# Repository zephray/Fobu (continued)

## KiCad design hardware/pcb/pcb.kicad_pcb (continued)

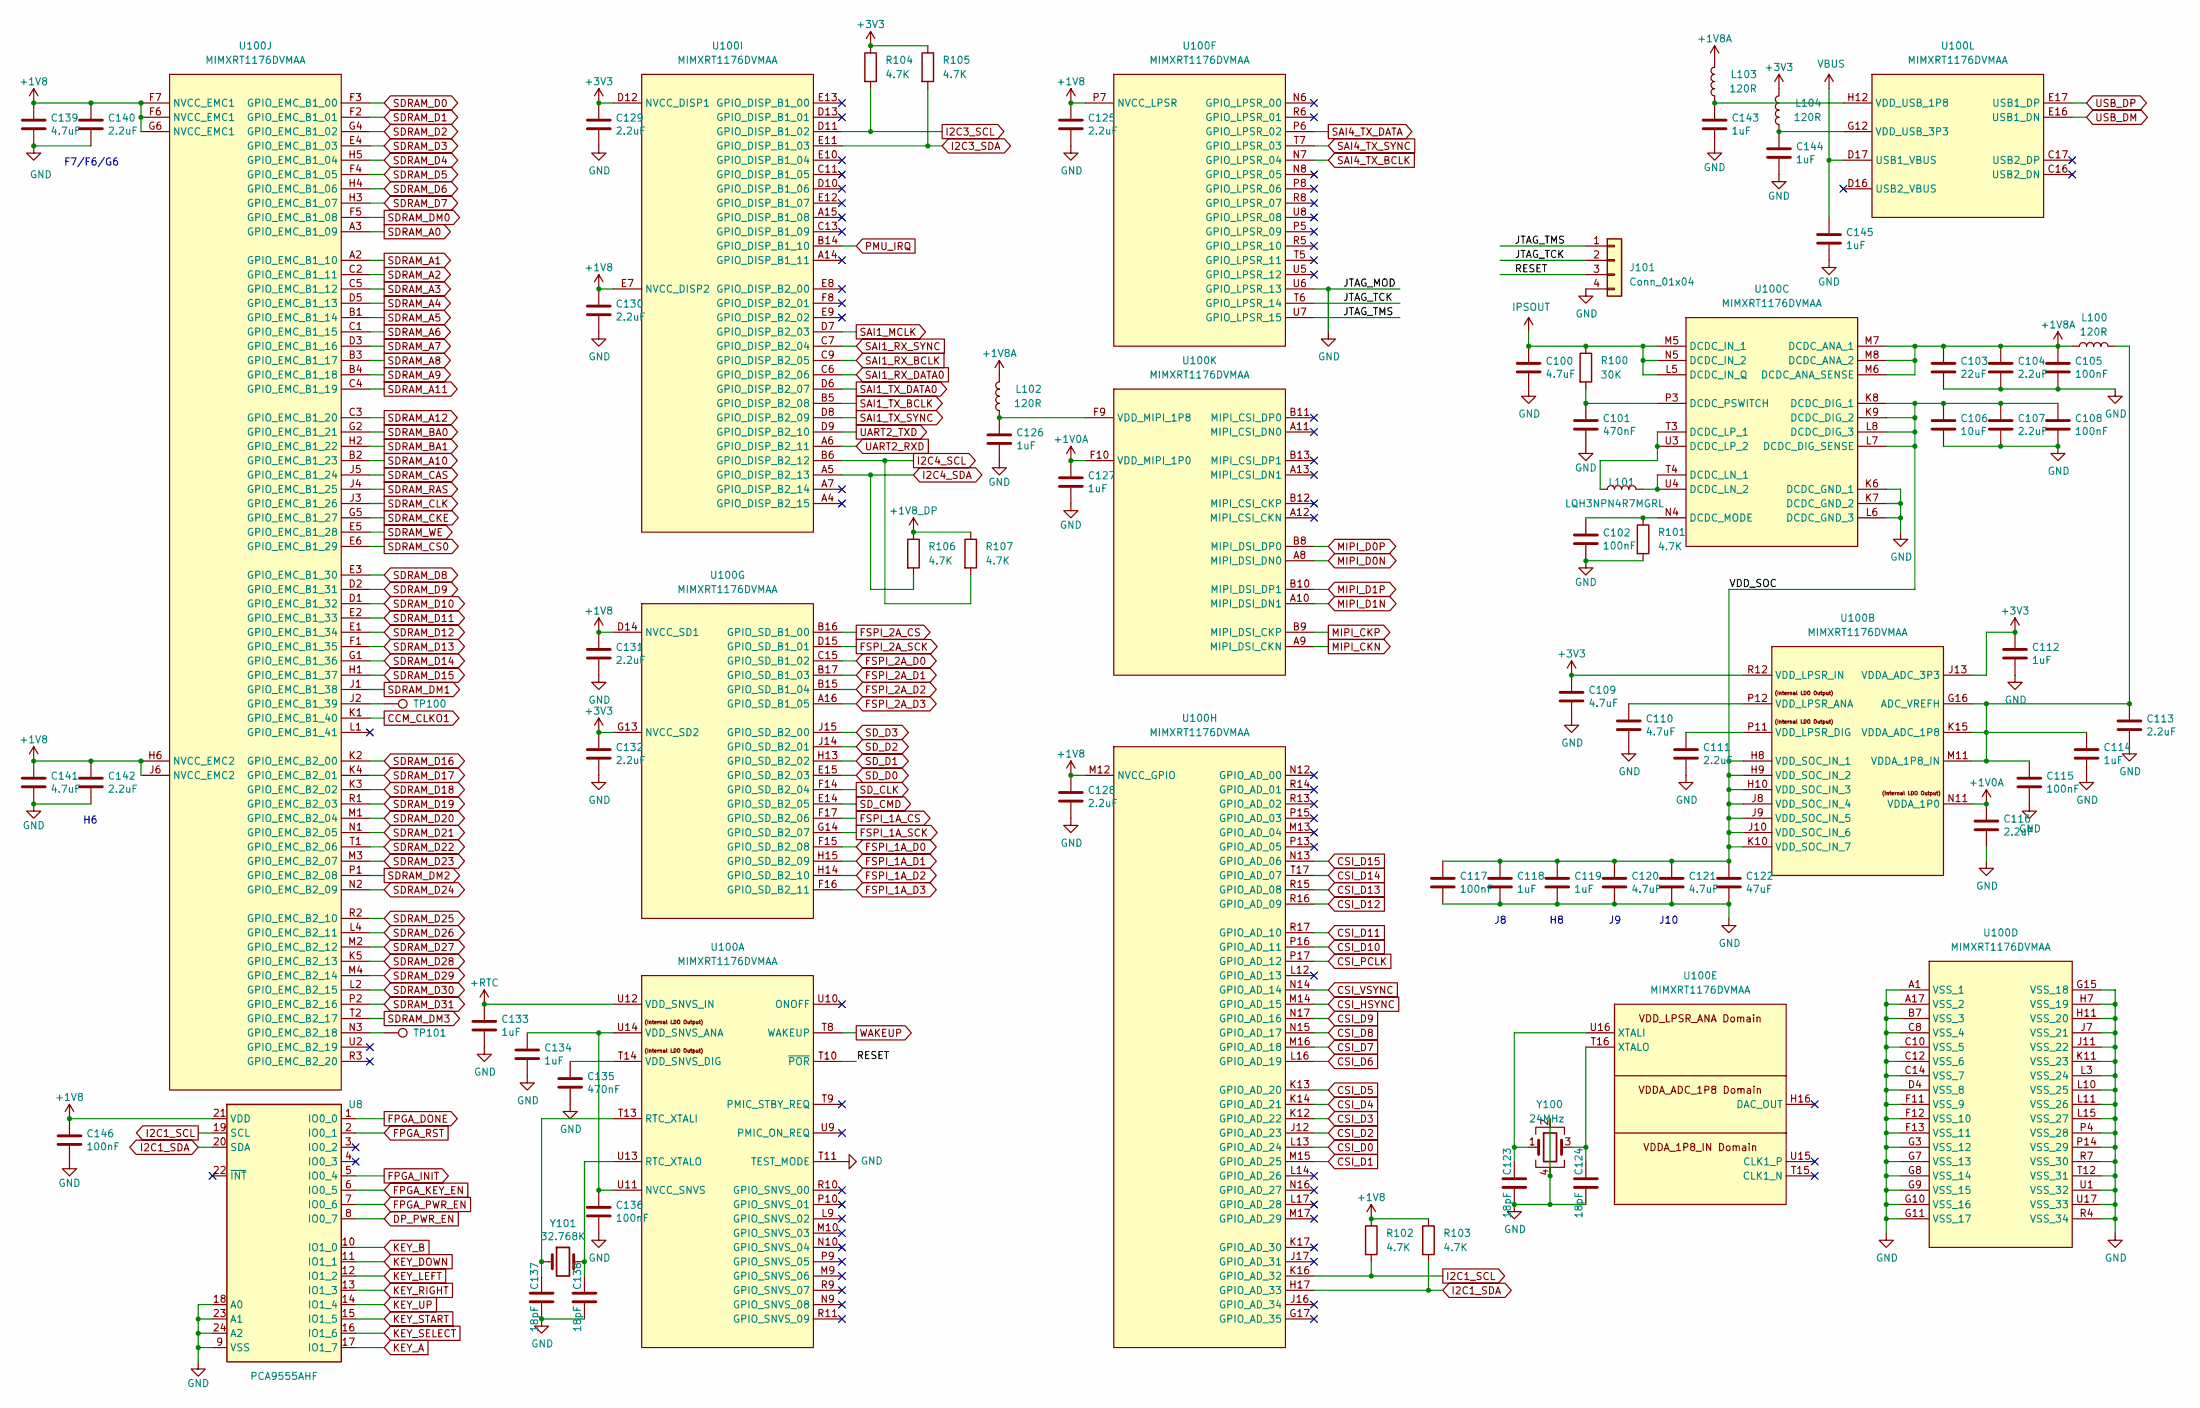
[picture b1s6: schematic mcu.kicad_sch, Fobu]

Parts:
C100, C109, C110, C120, C121, C139, C141: 4.7uF; C_0402_1005Metric
C101, C135: 470nF; C_0201_0603Metric
C102, C105, C108, C115, C117, C136, C146: 100nF; C_0201_0603Metric
C103: 22uF; C_0603_1608Metric
C104, C107, C111, C113, C116, C125, C128, C129, C130, C131, C132, C140, C142: 2.2uF; C_0402_1005Metric
C106: 10uF; C_0402_1005Metric
C112, C114, C118, C119, C126, C127, C133, C134, C143, C144, C145: 1uF; C_0402_1005Metric
C122: 47uF; C_0603_1608Metric
C123, C124, C137, C138: 18pF; C_0201_0603Metric
J101: Conn_01x04; PinHeader_1x04_P1.27mm_Vertical_SMD_Pin1Left
L100, L102, L103, L104: 120R; L_0402_1005Metric
L101: LQH3NPN4R7MGRL; L_Vishay_IHLP-1212
R100: 30K; R_0402_1005Metric
R101, R102, R103, R104, R105, R106, R107: 4.7K; R_0402_1005Metric
TP100, TP101: TestPoint; TestPoint_Pad_D0.5mm
U8: PCA9555AHF; HVQFN-24-1EP_4x4mm_P0.5mm_EP2.5x2.5mm
U100: MIMXRT1176DVMAA; BGA-289_17x17_14.0x14.0mm
Y100: 24MHz; Oscillator_SMD_Abracon_ASE-4Pin_3.2x2.5mm
Y101: 32.768K; Crystal_SMD_TXC_9HT11-2Pin_2.0x1.2mm_HandSoldering

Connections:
+1V0A: C116.1, C127.1, U100.F10 (VDD_MIPI_1P0), U100.N11 (VDDA_1P0)
+1V8: C125.1, C128.1, C130.1, C131.1, C139.1, C140.1, C141.1, C142.1, C146.1, R102.1, R103.1, U8.21 (VDD), U100.D14 (NVCC_SD1), U100.E7 (NVCC_DISP2), U100.F6 (NVCC_EMC1), U100.F7 (NVCC_EMC1), U100.G6 (NVCC_EMC1), U100.H6 (NVCC_EMC2), U100.J6 (NVCC_EMC2), U100.M12 (NVCC_GPIO), U100.P7 (NVCC_LPSR); also elsewhere on the board
+1V8A: C103.1, C104.1, C105.1, L100.1, L102.2, L103.2, U100.M6 (DCDC_ANA_SENSE), U100.M7 (DCDC_ANA_1), U100.M8 (DCDC_ANA_2); also elsewhere on the board
+1V8_DP: R106.1, R107.1; also elsewhere on the board
+3V3: C109.1, C112.1, C129.1, C132.1, L104.2, R104.1, R105.1, U100.D12 (NVCC_DISP1), U100.G13 (NVCC_SD2), U100.J13 (VDDA_ADC_3P3), U100.R12 (VDD_LPSR_IN); also elsewhere on the board
+RTC: C133.1, U100.U12 (VDD_SNVS_IN); also elsewhere on the board
/mcu/JTAG_TCK: J101.2, U100.T6 (GPIO_LPSR_14)
/mcu/JTAG_TMS: J101.1, U100.U7 (GPIO_LPSR_15)
/mcu/RESET: J101.3, U100.T10 (~POR)
/mcu/VDD_SOC: C106.1, C107.1, C108.1, C117.1, C118.1, C119.1, C120.1, C121.1, C122.1, U100.H8 (VDD_SOC_IN_1), U100.H9 (VDD_SOC_IN_2), U100.H10 (VDD_SOC_IN_3), U100.J8 (VDD_SOC_IN_4), U100.J9 (VDD_SOC_IN_5), U100.J10 (VDD_SOC_IN_6), U100.K8 (DCDC_DIG_1), U100.K9 (DCDC_DIG_2), U100.K10 (VDD_SOC_IN_7), U100.L7 (DCDC_DIG_SENSE), U100.L8 (DCDC_DIG_3)
CCM_CLKO1: U100.K1 (GPIO_EMC_B1_40)
CSI_D0: U100.L13 (GPIO_AD_24); also elsewhere on the board
CSI_D1: U100.M15 (GPIO_AD_25); also elsewhere on the board
CSI_D2: U100.J12 (GPIO_AD_23); also elsewhere on the board
CSI_D3: U100.K12 (GPIO_AD_22); also elsewhere on the board
CSI_D4: U100.K14 (GPIO_AD_21); also elsewhere on the board
CSI_D5: U100.K13 (GPIO_AD_20); also elsewhere on the board
CSI_D6: U100.L16 (GPIO_AD_19); also elsewhere on the board
CSI_D7: U100.M16 (GPIO_AD_18); also elsewhere on the board
CSI_D8: U100.N15 (GPIO_AD_17); also elsewhere on the board
CSI_D9: U100.N17 (GPIO_AD_16); also elsewhere on the board
CSI_D10: U100.P16 (GPIO_AD_11); also elsewhere on the board
CSI_D11: U100.R17 (GPIO_AD_10); also elsewhere on the board
CSI_D12: U100.R16 (GPIO_AD_09); also elsewhere on the board
CSI_D13: U100.R15 (GPIO_AD_08); also elsewhere on the board
CSI_D14: U100.T17 (GPIO_AD_07); also elsewhere on the board
CSI_D15: U100.N13 (GPIO_AD_06); also elsewhere on the board
CSI_HSYNC: U100.M14 (GPIO_AD_15); also elsewhere on the board
CSI_PCLK: U100.P17 (GPIO_AD_12); also elsewhere on the board
CSI_VSYNC: U100.N14 (GPIO_AD_14); also elsewhere on the board
DP_PWR_EN: U8.8 (IO0_7); also elsewhere on the board
FPGA_DONE: U8.1 (IO0_0); also elsewhere on the board
FPGA_INIT: U8.5 (IO0_4); also elsewhere on the board
FPGA_KEY_EN: U8.6 (IO0_5); also elsewhere on the board
FPGA_PWR_EN: U8.7 (IO0_6); also elsewhere on the board
FPGA_RST: U8.2 (IO0_1); also elsewhere on the board
FSPI_1A_CS: U100.F17 (GPIO_SD_B2_06); also elsewhere on the board
FSPI_1A_D0: U100.F15 (GPIO_SD_B2_08); also elsewhere on the board
FSPI_1A_D1: U100.H15 (GPIO_SD_B2_09); also elsewhere on the board
FSPI_1A_D2: U100.H14 (GPIO_SD_B2_10); also elsewhere on the board
FSPI_1A_D3: U100.F16 (GPIO_SD_B2_11); also elsewhere on the board
FSPI_1A_SCK: U100.G14 (GPIO_SD_B2_07); also elsewhere on the board
FSPI_2A_CS: U100.B16 (GPIO_SD_B1_00); also elsewhere on the board
FSPI_2A_D0: U100.C15 (GPIO_SD_B1_02); also elsewhere on the board
FSPI_2A_D1: U100.B17 (GPIO_SD_B1_03); also elsewhere on the board
FSPI_2A_D2: U100.B15 (GPIO_SD_B1_04); also elsewhere on the board
FSPI_2A_D3: U100.A16 (GPIO_SD_B1_05); also elsewhere on the board
FSPI_2A_SCK: U100.D15 (GPIO_SD_B1_01); also elsewhere on the board
GND: C100.2, C101.2, C102.2, C103.2, C104.2, C105.2, C106.2, C107.2, C108.2, C109.2, C110.2, C111.2, C112.2, C113.2, C114.2, C115.2, C116.2, C117.2, C118.2, C119.2, C120.2, C121.2, C122.2, C123.2, C124.2, C125.2, C126.2, C127.2, C128.2, C129.2, C130.2, C131.2, C132.2, C133.2, C134.2, C135.2, C136.2, C137.1, C138.1, C139.2, C140.2, C141.2, C142.2, C143.2, C144.2, C145.2, C146.2, J101.4, R101.2, U8.9 (VSS), U8.18 (A0), U8.23 (A1), U8.24 (A2), U100.A1 (VSS_1), U100.A17 (VSS_2), U100.B7 (VSS_3), U100.C8 (VSS_4), U100.C10 (VSS_5), U100.C12 (VSS_6), U100.C14 (VSS_7), U100.D4 (VSS_8), U100.F11 (VSS_9), U100.F12 (VSS_10), U100.F13 (VSS_11), U100.G3 (VSS_12), U100.G7 (VSS_13), U100.G8 (VSS_14), U100.G9 (VSS_15), U100.G10 (VSS_16), U100.G11 (VSS_17), U100.G15 (VSS_18), U100.H7 (VSS_19), U100.H11 (VSS_20), U100.J7 (VSS_21), U100.J11 (VSS_22), U100.K6 (DCDC_GND_1), U100.K7 (DCDC_GND_2), U100.K11 (VSS_23), U100.L3 (VSS_24), U100.L6 (DCDC_GND_3), U100.L10 (VSS_25), U100.L11 (VSS_26), U100.L15 (VSS_27), U100.P4 (VSS_28), U100.P14 (VSS_29), U100.R4 (VSS_34), U100.R7 (VSS_30), U100.T11 (TEST_MODE), U100.T12 (VSS_31), U100.U1 (VSS_32), U100.U6 (GPIO_LPSR_13), U100.U17 (VSS_33), Y100.2, Y100.4; also elsewhere on the board
I2C1_SCL: R102.2, U8.19 (SCL), U100.K16 (GPIO_AD_32); also elsewhere on the board
I2C1_SDA: R103.2, U8.20 (SDA), U100.H17 (GPIO_AD_33); also elsewhere on the board
I2C3_SCL: R104.2, U100.D11 (GPIO_DISP_B1_02); also elsewhere on the board
I2C3_SDA: R105.2, U100.E11 (GPIO_DISP_B1_03); also elsewhere on the board
I2C4_SCL: R107.2, U100.B6 (GPIO_DISP_B2_12); also elsewhere on the board
I2C4_SDA: R106.2, U100.A5 (GPIO_DISP_B2_13); also elsewhere on the board
IPSOUT: C100.1, R100.1, U100.L5 (DCDC_IN_Q), U100.M5 (DCDC_IN_1), U100.N5 (DCDC_IN_2); also elsewhere on the board
KEY_A: U8.17 (IO1_7); also elsewhere on the board
KEY_B: U8.10 (IO1_0); also elsewhere on the board
KEY_DOWN: U8.11 (IO1_1); also elsewhere on the board
KEY_LEFT: U8.12 (IO1_2); also elsewhere on the board
KEY_RIGHT: U8.13 (IO1_3); also elsewhere on the board
KEY_SELECT: U8.16 (IO1_6); also elsewhere on the board
KEY_START: U8.15 (IO1_5); also elsewhere on the board
KEY_UP: U8.14 (IO1_4); also elsewhere on the board
MIPI_CKN: U100.A9 (MIPI_DSI_CKN); also elsewhere on the board
MIPI_CKP: U100.B9 (MIPI_DSI_CKP); also elsewhere on the board
MIPI_D0N: U100.A8 (MIPI_DSI_DN0); also elsewhere on the board
MIPI_D0P: U100.B8 (MIPI_DSI_DP0); also elsewhere on the board
MIPI_D1N: U100.A10 (MIPI_DSI_DN1); also elsewhere on the board
MIPI_D1P: U100.B10 (MIPI_DSI_DP1); also elsewhere on the board
unnamed: C101.1, R100.2, U100.P3 (DCDC_PSWITCH)
unnamed: C102.1, R101.1, U100.N4 (DCDC_MODE)
unnamed: C110.1, U100.P12 (VDD_LPSR_ANA)
unnamed: C111.1, U100.P11 (VDD_LPSR_DIG)
unnamed: C113.1, C114.1, C115.1, L100.2, U100.G16 (ADC_VREFH), U100.K15 (VDDA_ADC_1P8), U100.M11 (VDDA_1P8_IN)
unnamed: C123.1, U100.U16 (XTALI), Y100.1
unnamed: C124.1, U100.T16 (XTALO), Y100.3
unnamed: C126.1, L102.1, U100.F9 (VDD_MIPI_1P8)
unnamed: C134.1, C136.1, U100.U11 (NVCC_SNVS), U100.U14 (VDD_SNVS_ANA)
unnamed: C135.1, U100.T14 (VDD_SNVS_DIG)
unnamed: C137.2, U100.T13 (RTC_XTALI), Y101.1
unnamed: C138.2, U100.U13 (RTC_XTALO), Y101.2
unnamed: C143.1, L103.1, U100.H12 (VDD_USB_1P8)
unnamed: C144.1, L104.1, U100.G12 (VDD_USB_3P3)
unnamed: L101.1, U100.T3 (DCDC_LP_1), U100.U3 (DCDC_LP_2)
unnamed: L101.2, U100.T4 (DCDC_LN_1), U100.U4 (DCDC_LN_2)
unnamed: TP100.1, U100.J2 (GPIO_EMC_B1_39)
unnamed: TP101.1, U100.N3 (GPIO_EMC_B2_18)
PMU_IRQ: U100.B14 (GPIO_DISP_B1_10); also elsewhere on the board
SAI1_MCLK: U100.D7 (GPIO_DISP_B2_03); also elsewhere on the board
SAI1_RX_BCLK: U100.C9 (GPIO_DISP_B2_05); also elsewhere on the board
SAI1_RX_DATA0: U100.C6 (GPIO_DISP_B2_06); also elsewhere on the board
SAI1_RX_SYNC: U100.C7 (GPIO_DISP_B2_04); also elsewhere on the board
SAI1_TX_BCLK: U100.B5 (GPIO_DISP_B2_08); also elsewhere on the board
SAI1_TX_DATA0: U100.D6 (GPIO_DISP_B2_07); also elsewhere on the board
SAI1_TX_SYNC: U100.D8 (GPIO_DISP_B2_09); also elsewhere on the board
SAI4_TX_BCLK: U100.N7 (GPIO_LPSR_04); also elsewhere on the board
SAI4_TX_DATA: U100.P6 (GPIO_LPSR_02); also elsewhere on the board
SAI4_TX_SYNC: U100.T7 (GPIO_LPSR_03); also elsewhere on the board
SDRAM_A0: U100.A3 (GPIO_EMC_B1_09); also elsewhere on the board
SDRAM_A1: U100.A2 (GPIO_EMC_B1_10); also elsewhere on the board
SDRAM_A2: U100.C2 (GPIO_EMC_B1_11); also elsewhere on the board
SDRAM_A3: U100.C5 (GPIO_EMC_B1_12); also elsewhere on the board
SDRAM_A4: U100.D5 (GPIO_EMC_B1_13); also elsewhere on the board
SDRAM_A5: U100.B1 (GPIO_EMC_B1_14); also elsewhere on the board
SDRAM_A6: U100.C1 (GPIO_EMC_B1_15); also elsewhere on the board
SDRAM_A7: U100.D3 (GPIO_EMC_B1_16); also elsewhere on the board
SDRAM_A8: U100.B3 (GPIO_EMC_B1_17); also elsewhere on the board
SDRAM_A9: U100.B4 (GPIO_EMC_B1_18); also elsewhere on the board
SDRAM_A10: U100.B2 (GPIO_EMC_B1_23); also elsewhere on the board
SDRAM_A11: U100.C4 (GPIO_EMC_B1_19); also elsewhere on the board
SDRAM_A12: U100.C3 (GPIO_EMC_B1_20); also elsewhere on the board
SDRAM_BA0: U100.G2 (GPIO_EMC_B1_21); also elsewhere on the board
SDRAM_BA1: U100.H2 (GPIO_EMC_B1_22); also elsewhere on the board
SDRAM_CAS: U100.J5 (GPIO_EMC_B1_24); also elsewhere on the board
SDRAM_CKE: U100.G5 (GPIO_EMC_B1_27); also elsewhere on the board
SDRAM_CLK: U100.J3 (GPIO_EMC_B1_26); also elsewhere on the board
SDRAM_CS0: U100.E6 (GPIO_EMC_B1_29); also elsewhere on the board
SDRAM_D0: U100.F3 (GPIO_EMC_B1_00); also elsewhere on the board
SDRAM_D1: U100.F2 (GPIO_EMC_B1_01); also elsewhere on the board
SDRAM_D2: U100.G4 (GPIO_EMC_B1_02); also elsewhere on the board
SDRAM_D3: U100.E4 (GPIO_EMC_B1_03); also elsewhere on the board
SDRAM_D4: U100.H5 (GPIO_EMC_B1_04); also elsewhere on the board
SDRAM_D5: U100.F4 (GPIO_EMC_B1_05); also elsewhere on the board
SDRAM_D6: U100.H4 (GPIO_EMC_B1_06); also elsewhere on the board
SDRAM_D7: U100.H3 (GPIO_EMC_B1_07); also elsewhere on the board
SDRAM_D8: U100.E3 (GPIO_EMC_B1_30); also elsewhere on the board
SDRAM_D9: U100.D2 (GPIO_EMC_B1_31); also elsewhere on the board
SDRAM_D10: U100.D1 (GPIO_EMC_B1_32); also elsewhere on the board
SDRAM_D11: U100.E2 (GPIO_EMC_B1_33); also elsewhere on the board
SDRAM_D12: U100.E1 (GPIO_EMC_B1_34); also elsewhere on the board
SDRAM_D13: U100.F1 (GPIO_EMC_B1_35); also elsewhere on the board
SDRAM_D14: U100.G1 (GPIO_EMC_B1_36); also elsewhere on the board
SDRAM_D15: U100.H1 (GPIO_EMC_B1_37); also elsewhere on the board
SDRAM_D16: U100.K2 (GPIO_EMC_B2_00); also elsewhere on the board
SDRAM_D17: U100.K4 (GPIO_EMC_B2_01); also elsewhere on the board
SDRAM_D18: U100.K3 (GPIO_EMC_B2_02); also elsewhere on the board
SDRAM_D19: U100.R1 (GPIO_EMC_B2_03); also elsewhere on the board
SDRAM_D20: U100.M1 (GPIO_EMC_B2_04); also elsewhere on the board
SDRAM_D21: U100.N1 (GPIO_EMC_B2_05); also elsewhere on the board
SDRAM_D22: U100.T1 (GPIO_EMC_B2_06); also elsewhere on the board
SDRAM_D23: U100.M3 (GPIO_EMC_B2_07); also elsewhere on the board
SDRAM_D24: U100.N2 (GPIO_EMC_B2_09); also elsewhere on the board
SDRAM_D25: U100.R2 (GPIO_EMC_B2_10); also elsewhere on the board
SDRAM_D26: U100.L4 (GPIO_EMC_B2_11); also elsewhere on the board
SDRAM_D27: U100.M2 (GPIO_EMC_B2_12); also elsewhere on the board
SDRAM_D28: U100.K5 (GPIO_EMC_B2_13); also elsewhere on the board
SDRAM_D29: U100.M4 (GPIO_EMC_B2_14); also elsewhere on the board
SDRAM_D30: U100.L2 (GPIO_EMC_B2_15); also elsewhere on the board
SDRAM_D31: U100.P2 (GPIO_EMC_B2_16); also elsewhere on the board
SDRAM_DM0: U100.F5 (GPIO_EMC_B1_08); also elsewhere on the board
SDRAM_DM1: U100.J1 (GPIO_EMC_B1_38); also elsewhere on the board
SDRAM_DM2: U100.P1 (GPIO_EMC_B2_08); also elsewhere on the board
SDRAM_DM3: U100.T2 (GPIO_EMC_B2_17); also elsewhere on the board
SDRAM_RAS: U100.J4 (GPIO_EMC_B1_25); also elsewhere on the board
SDRAM_WE: U100.E5 (GPIO_EMC_B1_28); also elsewhere on the board
SD_CLK: U100.F14 (GPIO_SD_B2_04); also elsewhere on the board
SD_CMD: U100.E14 (GPIO_SD_B2_05); also elsewhere on the board
SD_D0: U100.E15 (GPIO_SD_B2_03); also elsewhere on the board
SD_D1: U100.H13 (GPIO_SD_B2_02); also elsewhere on the board
SD_D2: U100.J14 (GPIO_SD_B2_01); also elsewhere on the board
SD_D3: U100.J15 (GPIO_SD_B2_00); also elsewhere on the board
UART2_RXD: U100.A6 (GPIO_DISP_B2_11); also elsewhere on the board
UART2_TXD: U100.D9 (GPIO_DISP_B2_10); also elsewhere on the board
USB_DM: U100.E16 (USB1_DN); also elsewhere on the board
USB_DP: U100.E17 (USB1_DP); also elsewhere on the board
VBUS: C145.1, U100.D17 (USB1_VBUS); also elsewhere on the board
WAKEUP: U100.T8 (WAKEUP); also elsewhere on the board

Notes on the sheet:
F7/F6/G6
J10

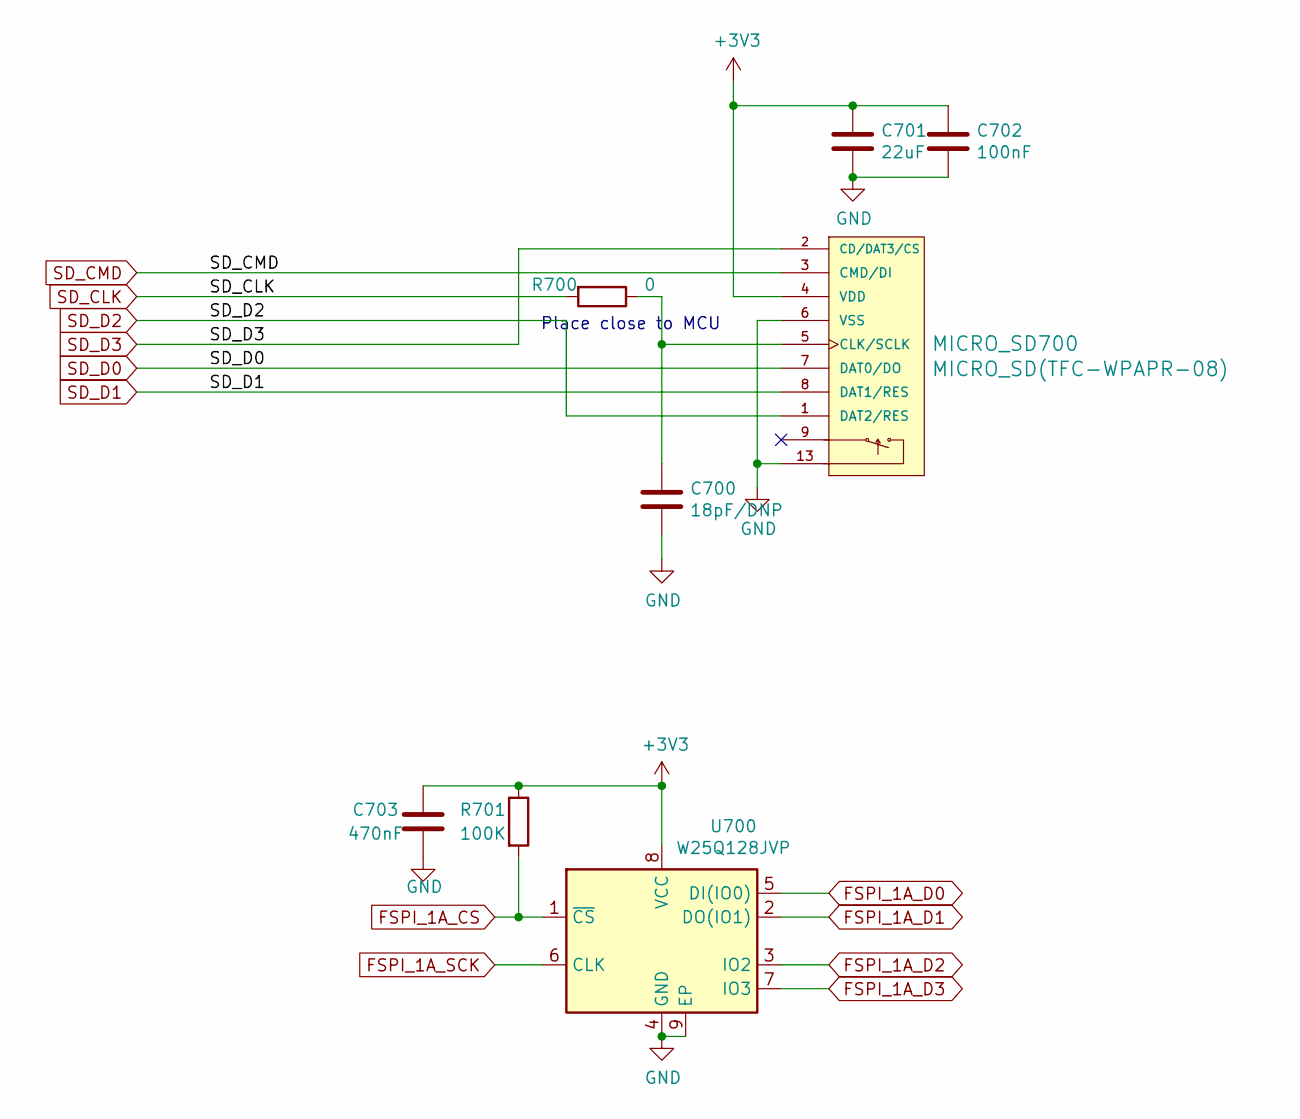
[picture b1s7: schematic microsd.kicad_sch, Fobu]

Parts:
C700: 18pF/DNP; C_0201_0603Metric
C701: 22uF; C_0603_1608Metric
C702: 100nF; C_0201_0603Metric
C703: 470nF; C_0201_0603Metric
MICRO_SD700: MICRO_SD(TFC-WPAPR-08); TFC-WPAPR-08
R700: 0; R_0402_1005Metric
R701: 100K; C_0402_1005Metric
U700: W25Q128JVP; WSON-8-1EP_6x5mm_P1.27mm_EP3.4x4.3mm

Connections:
+3V3: C701.1, C702.1, C703.2, MICRO_SD700.4 (VDD), R701.1, U700.8 (VCC); also elsewhere on the board
FSPI_1A_CS: R701.2, U700.1 (~CS); also elsewhere on the board
FSPI_1A_D0: U700.5 (DI(IO0)); also elsewhere on the board
FSPI_1A_D1: U700.2 (DO(IO1)); also elsewhere on the board
FSPI_1A_D2: U700.3 (IO2); also elsewhere on the board
FSPI_1A_D3: U700.7 (IO3); also elsewhere on the board
FSPI_1A_SCK: U700.6 (CLK); also elsewhere on the board
GND: C700.2, C701.2, C702.2, C703.1, MICRO_SD700.6 (VSS), MICRO_SD700.10, MICRO_SD700.11, MICRO_SD700.12, MICRO_SD700.13, U700.4 (GND), U700.9 (EP); also elsewhere on the board
unnamed: C700.1, MICRO_SD700.5 (CLK/SCLK), R700.1
SD_CLK: R700.2; also elsewhere on the board
SD_CMD: MICRO_SD700.3 (CMD/DI); also elsewhere on the board
SD_D0: MICRO_SD700.7 (DAT0/DO); also elsewhere on the board
SD_D1: MICRO_SD700.8 (DAT1/RES); also elsewhere on the board
SD_D2: MICRO_SD700.1 (DAT2/RES); also elsewhere on the board
SD_D3: MICRO_SD700.2 (CD/DAT3/CS); also elsewhere on the board

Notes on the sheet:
Place close to MCU

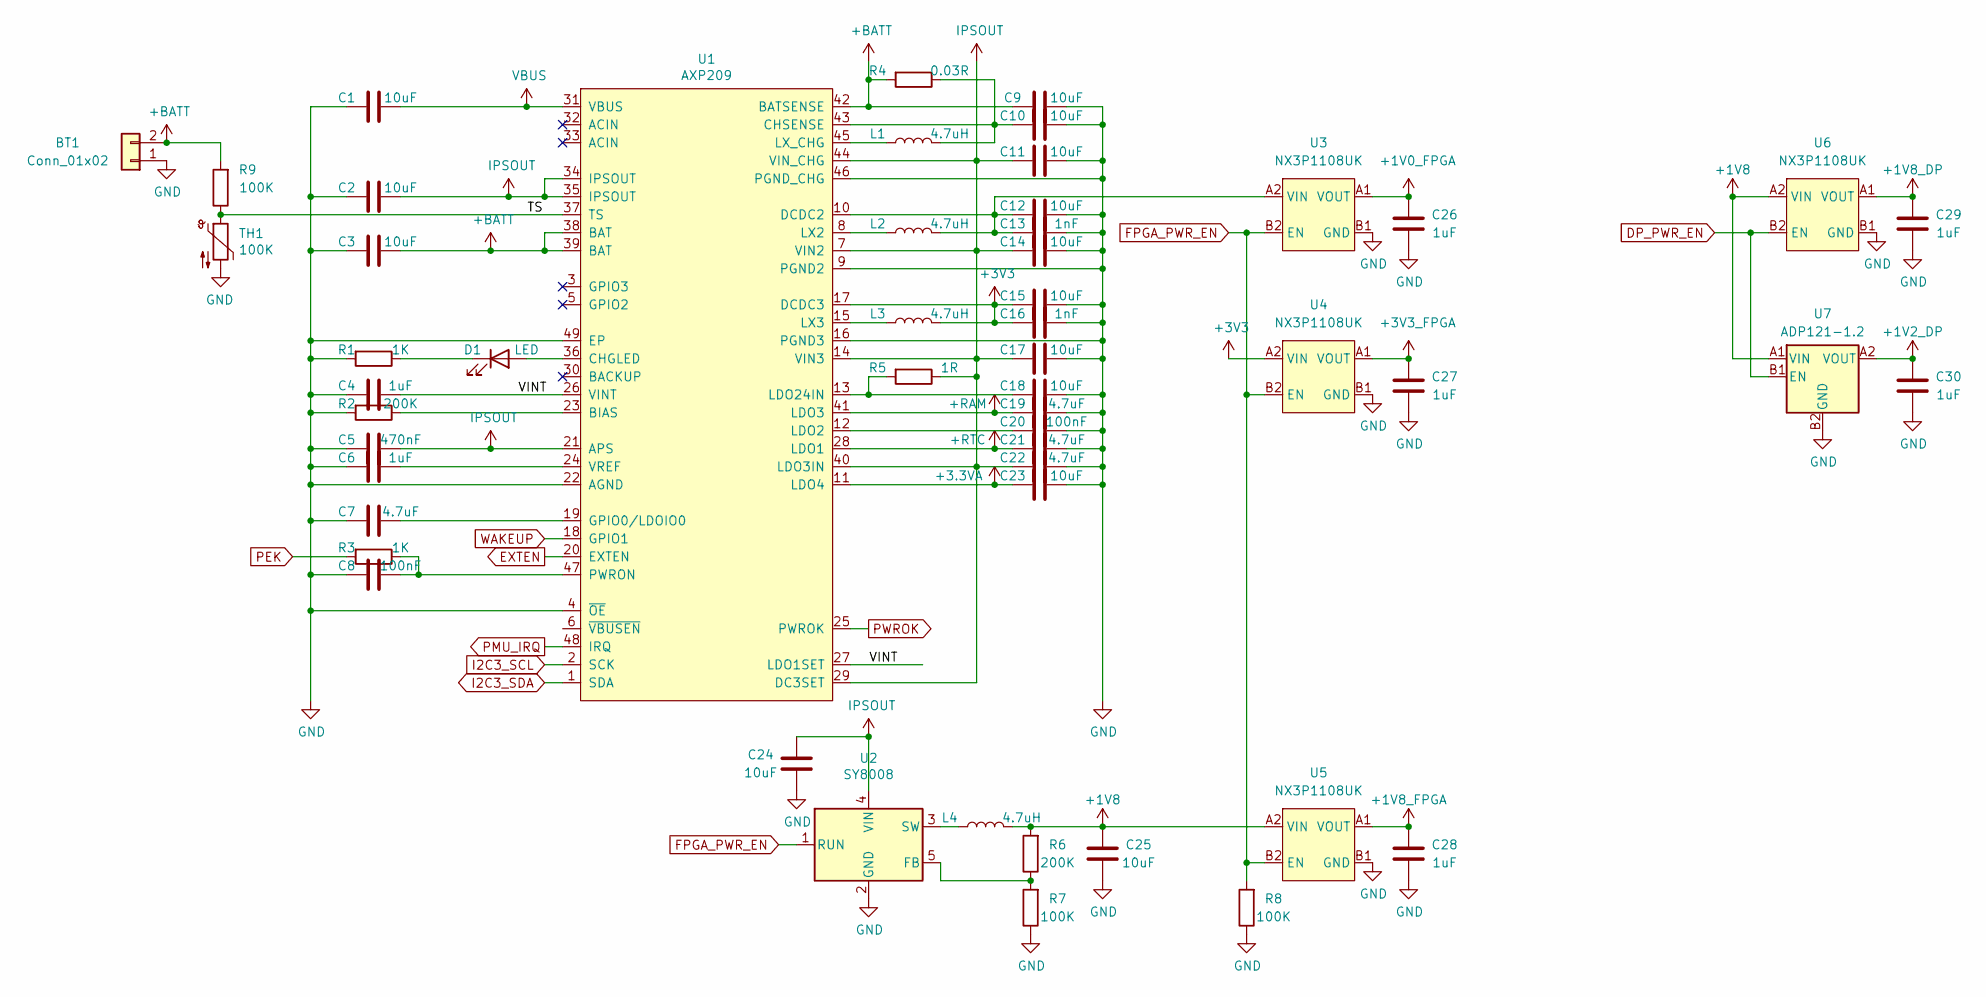
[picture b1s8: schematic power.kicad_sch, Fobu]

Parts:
BT1: Conn_01x02; Molex_PicoBlade_53261-0271_1x02-1MP_P1.25mm_Horizontal
C1, C2, C3, C9, C10, C11, C12, C14, C15, C17, C18, C23, C24, C25: 10uF; C_0402_1005Metric
C4, C6, C26, C27, C28, C29, C30: 1uF; C_0402_1005Metric
C5: 470nF; C_0201_0603Metric
C7, C19, C21, C22: 4.7uF; C_0402_1005Metric
C8, C20: 100nF; C_0201_0603Metric
C13, C16: 1nF; C_0402_1005Metric
D1: LED; D_0603_1608Metric
L1, L2, L3, L4: 4.7uH; L_1008_2520Metric
R1, R3: 1K; R_0402_1005Metric
R2, R6: 200K; R_0402_1005Metric
R4: 0.03R; R_0805_2012Metric
R5: 1R; R_0603_1608Metric
R7, R8, R9: 100K; R_0402_1005Metric
TH1: 100K; R_0603_1608Metric
U1: AXP209; QFN-48-1EP_6x6mm_P0.4mm_EP4.2x4.2mm_ThermalVias
U2: SY8008; TSOT-23-5
U3, U4, U5, U6: NX3P1108UK; WLCSP-4-X1-WLB0909-4_0.89x0.89mm_P0.5mm
U7: ADP121-1.2; CSP-4_2x2_0.8x0.8mm

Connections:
+1V0_FPGA: C26.2, U3.A1 (VOUT); also elsewhere on the board
+1V2_DP: C30.2, U7.A2 (VOUT); also elsewhere on the board
+1V8: C25.2, L4.2, R6.2, U5.A2 (VIN), U6.A2 (VIN), U7.A1 (VIN); also elsewhere on the board
+1V8_DP: C29.2, U6.A1 (VOUT); also elsewhere on the board
+3.3VA: C23.2, U1.11 (LDO4); also elsewhere on the board
+3V3: C15.2, C16.2, L3.2, U1.17 (DCDC3), U4.A2 (VIN); also elsewhere on the board
+3V3_FPGA: C27.2, U4.A1 (VOUT)
+BATT: BT1.2, C3.1, C9.2, R4.2, R9.2, U1.38 (BAT), U1.39 (BAT), U1.42 (BATSENSE)
+RAM: C19.2, U1.41 (LDO3); also elsewhere on the board
+RTC: C21.2, U1.28 (LDO1); also elsewhere on the board
/power/TS: R9.1, TH1.1, U1.37 (TS)
/power/VINT: C4.1, U1.26 (VINT), U1.27 (LDO1SET)
DP_PWR_EN: U6.B2 (EN), U7.B1 (EN); also elsewhere on the board
EXTEN: U1.20 (EXTEN)
FPGA_PWR_EN: R8.2, U2.1 (RUN), U3.B2 (EN), U4.B2 (EN), U5.B2 (EN); also elsewhere on the board
GND: BT1.1, C1.2, C2.2, C3.2, C4.2, C5.2, C6.2, C7.2, C8.2, C9.1, C10.1, C11.1, C12.1, C13.1, C14.1, C15.1, C16.1, C17.1, C18.1, C19.1, C20.1, C21.1, C22.1, C23.1, C24.1, C25.1, C26.1, C27.1, C28.1, C29.1, C30.1, R1.2, R2.2, R7.1, R8.1, TH1.2, U1.4 (~OE), U1.9 (PGND2), U1.16 (PGND3), U1.22 (AGND), U1.46 (PGND_CHG), U1.49 (EP), U2.2 (GND), U3.B1 (GND), U4.B1 (GND), U5.B1 (GND), U6.B1 (GND), U7.B2 (GND); also elsewhere on the board
I2C3_SCL: U1.2 (SCK); also elsewhere on the board
I2C3_SDA: U1.1 (SDA); also elsewhere on the board
IPSOUT: C2.1, C5.1, C11.2, C14.2, C17.2, C22.2, C24.2, R5.1, U1.7 (VIN2), U1.14 (VIN3), U1.21 (APS), U1.29 (DC3SET), U1.34 (IPSOUT), U1.35 (IPSOUT), U1.40 (LDO3IN), U1.44 (VIN_CHG), U2.4 (VIN); also elsewhere on the board
unnamed: C6.1, U1.24 (VREF)
unnamed: C7.1, U1.19 (GPIO0/LDOIO0)
unnamed: C8.1, R3.1, U1.47 (PWRON)
unnamed: C10.2, L1.2, R4.1, U1.43 (CHSENSE)
unnamed: C12.2, C13.2, L2.2, U1.10 (DCDC2), U3.A2 (VIN)
unnamed: C18.2, R5.2, U1.13 (LDO24IN)
unnamed: C20.2, U1.12 (LDO2)
unnamed: D1.1 (K), R1.1
unnamed: D1.2 (A), U1.36 (CHGLED)
unnamed: L1.1, U1.45 (LX_CHG)
unnamed: L2.1, U1.8 (LX2)
unnamed: L3.1, U1.15 (LX3)
unnamed: L4.1, U2.3 (SW)
unnamed: R2.1, U1.23 (BIAS)
unnamed: R6.1, R7.2, U2.5 (FB)
PEK: R3.2; also elsewhere on the board
PMU_IRQ: U1.48 (IRQ); also elsewhere on the board
PWROK: U1.25 (PWROK)
VBUS: C1.1, U1.31 (VBUS); also elsewhere on the board
WAKEUP: U1.18 (GPIO1); also elsewhere on the board
